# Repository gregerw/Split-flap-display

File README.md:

# Split-flap-display
Self-made split flap display

Find instructions how to build display at [https://splitflap.home.blog/](https://splitflap.home.blog/)

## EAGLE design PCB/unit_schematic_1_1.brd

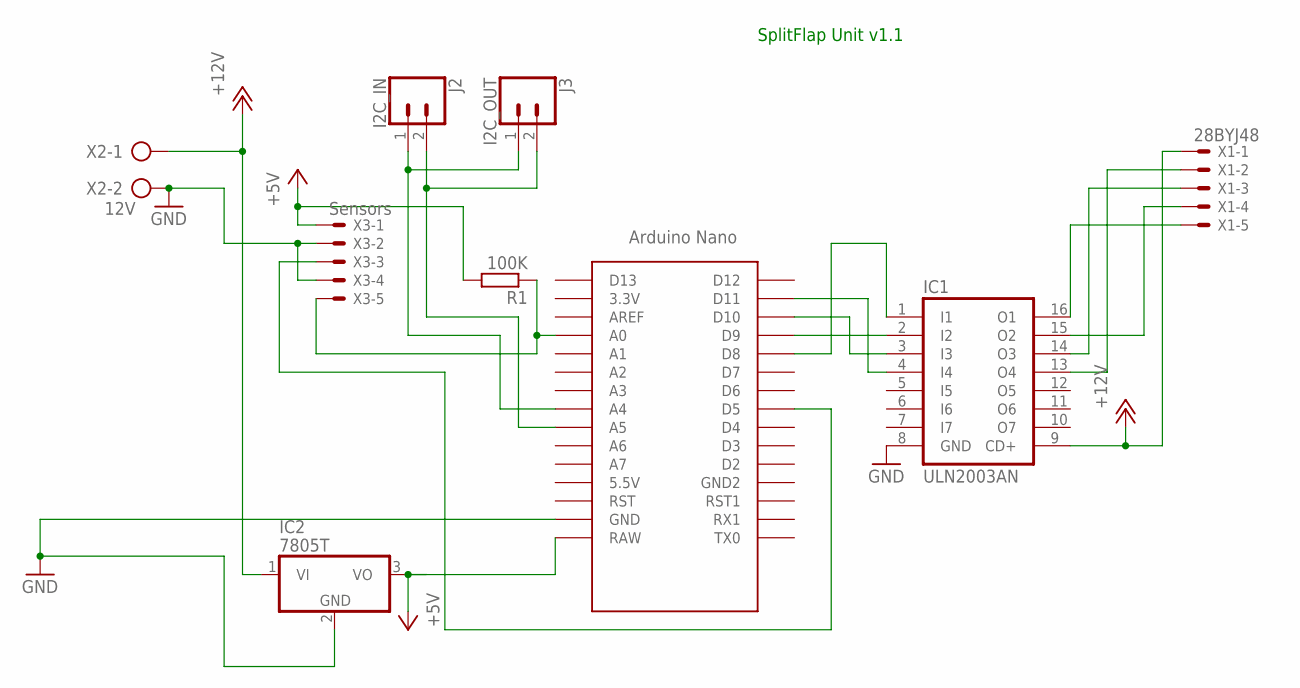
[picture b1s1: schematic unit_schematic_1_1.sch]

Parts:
IC1: ULN2003AN; DIL16
IC2: 7805T; TO220H
J2: I2C_IN; JST-2-PTH
J3: I2C_OUT; JST-2-PTH
R1: 100K; 0207/10
U$2: NANO
X1: 28BYJ48; JST-XH-05-PACKAGE-ROUND-PAD
X2: 12V; AK300/2
X3: Sensors; JST-XH-05-PACKAGE-ROUND-PAD

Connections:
+5V: IC2.3 (VO), R1.2, U$2.RAW, X3.1
+12V: IC1.9 (CD+), IC2.1 (VI), X1.1, X2.1
GND: IC1.8 (GND), IC2.2 (GND), U$2.GND, X2.2, X3.2, X3.4
unnamed: IC1.1 (I1), U$2.D8
unnamed: R1.1, U$2.A0, X3.5
unnamed: IC1.2 (I2), U$2.D9
unnamed: IC1.3 (I3), U$2.D10
unnamed: IC1.4 (I4), U$2.D11
unnamed: IC1.13 (O4), X1.2
unnamed: IC1.14 (O3), X1.3
unnamed: IC1.15 (O2), X1.4
unnamed: IC1.16 (O1), X1.5
unnamed: U$2.D5, X3.3
unnamed: J2.2, J3.2, U$2.A5
unnamed: J2.1, J3.1, U$2.A4

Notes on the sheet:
SplitFlap Unit v1.1

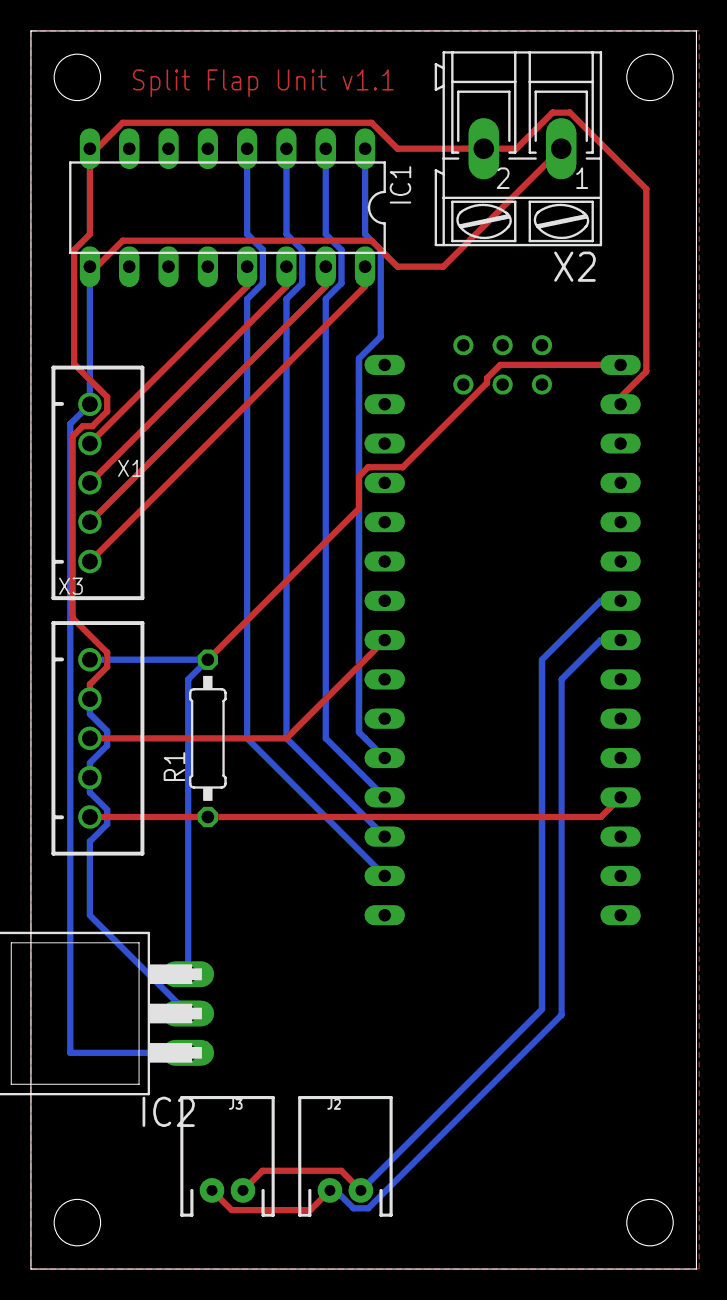
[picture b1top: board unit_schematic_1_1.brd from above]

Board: 2 copper layers, 43.0 x 80.0 mm, 9 parts (0 on the bottom side), 15 nets.

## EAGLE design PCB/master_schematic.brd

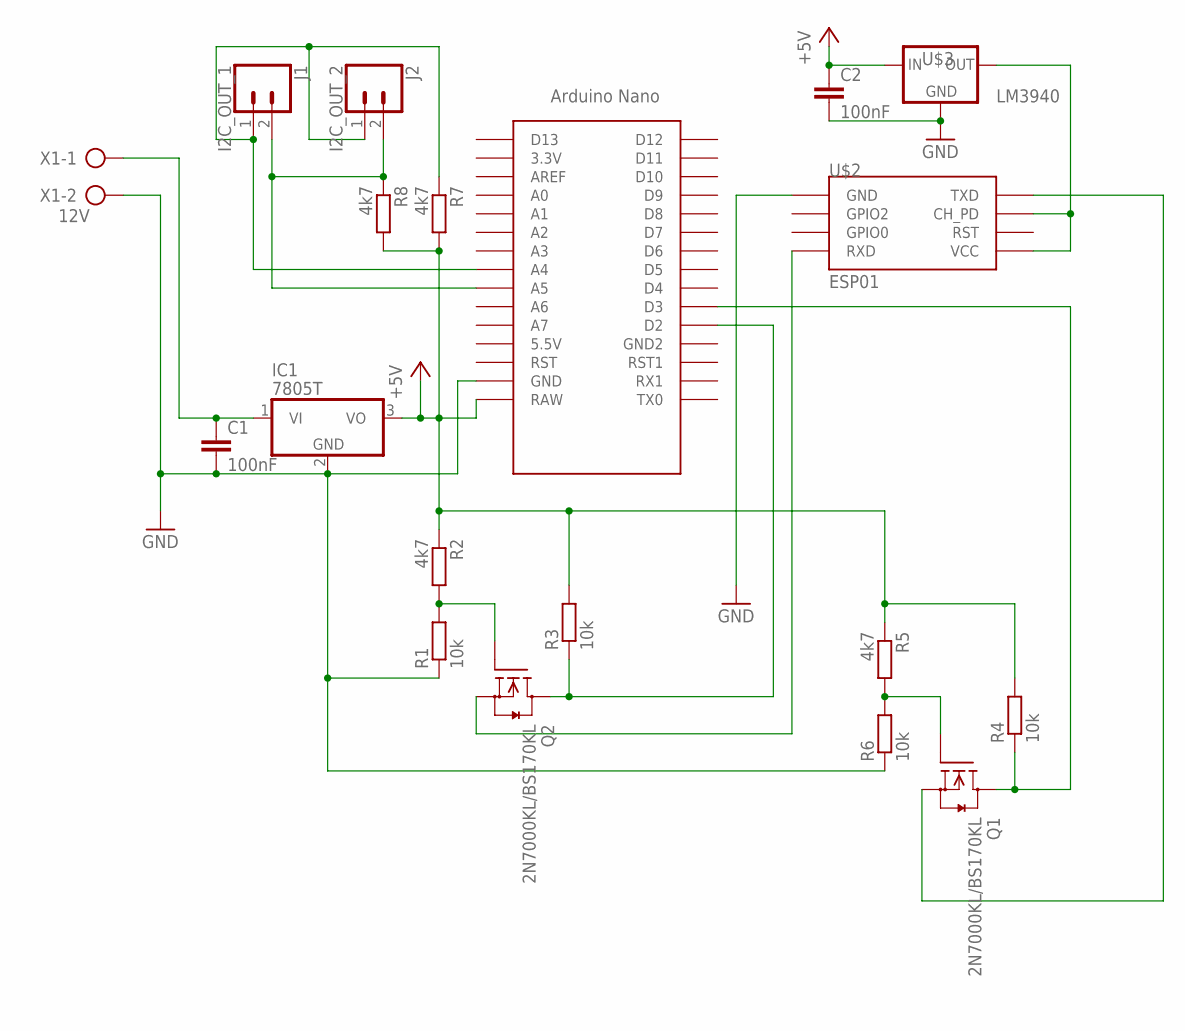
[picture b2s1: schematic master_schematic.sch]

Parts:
C1, C2: 100nF; C025-030X050
IC1: 7805T; TO220H
J1: I2C_OUT_1; JST-2-PTH
J2: I2C_OUT_2; JST-2-PTH
Q1, Q2: 2N7000KL/BS170KL; TO92
R1, R3, R4, R6: 10k; 0207/10
R2, R5, R7, R8: 4k7; 0207/10
U$1: NANO
U$2: ESP01
U$3: LM3940; TO220
X1: 12V; AK300/2

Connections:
+5V: C2.1, IC1.3 (VO), R2.1, R3.2, R4.2, R5.1, R7.2, R8.2, U$1.RAW, U$3.1 (IN)
GND: C1.2, C2.2, IC1.2 (GND), R1.1, R6.1, U$1.GND, U$2.GND, U$3.2 (GND), X1.2
unnamed: J1.1, J2.1, R7.1, U$1.A4
unnamed: J1.2, J2.2, R8.1, U$1.A5
unnamed: C1.1, IC1.1 (VI), X1.1
unnamed: Q2.1 (S), U$2.RX (RXD)
unnamed: Q2.2 (G), R1.2, R2.2
unnamed: U$2.CH_PD, U$2.VCC, U$3.3 (OUT)
unnamed: Q1.2 (G), R5.2, R6.2
unnamed: Q1.3 (D), R4.1, U$1.D3
unnamed: Q2.3 (D), R3.1, U$1.D2
unnamed: Q1.1 (S), U$2.TX (TXD)

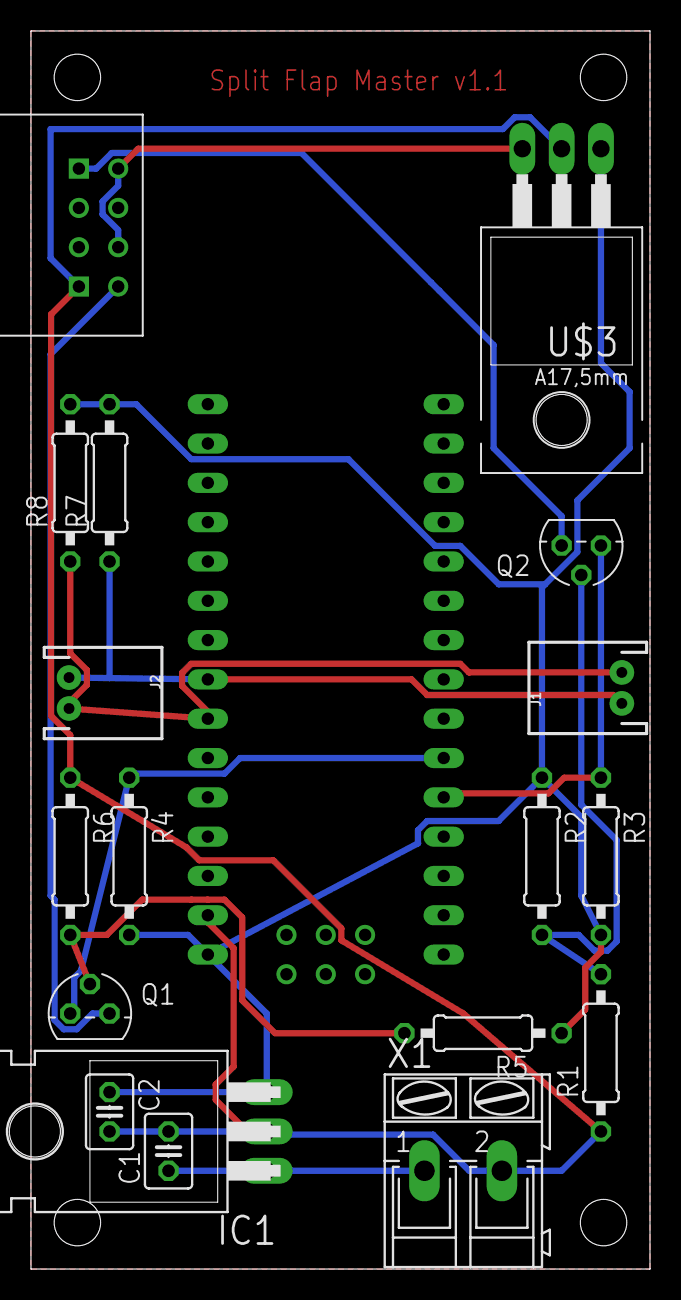
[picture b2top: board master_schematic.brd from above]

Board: 2 copper layers, 40.0 x 80.0 mm, 19 parts (0 on the bottom side), 12 nets.

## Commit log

2019-03-03 Update BOM_split_flap.xlsx
    fixed some entries
2019-03-05 initially source
2019-03-05 intially upload
2019-03-05 Create temp
2019-03-05 initial upload
2019-03-05 delete
2019-05-17 Update BOM_split_flap.xlsx
    Added components for v1.1
2019-05-17 new versions of pcb
2019-05-17 CAD files for unit
2019-05-17 clean version
2019-05-18 is not part of the cad lib
2019-05-18 not part of pcba files
2019-05-18 invisble file
2019-05-18 not needed
2019-05-18 initial version
2019-08-03 Create flapDrawing.PDF
    Drawing of single flap
2021-08-26 Added 3d printable .stl flap file
2023-11-09 Fix Hyperlink in README.md

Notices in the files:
parts and their libraries:
SparkFun-Connectors: Licensing: Creative Commons ShareAlike 4.0 International - https://creativecommons.org/licenses/by-sa/4.0
m-pad-2.1: License : GNU General Public License version 2 (see bottom)
